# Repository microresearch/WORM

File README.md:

The WORM was for a long time desirous to speake, but the rule and
or∣der of the Court enjoyned him silence, but now strutting and
swelling, and impatient, of further delay, he broke out thus... [Maier]

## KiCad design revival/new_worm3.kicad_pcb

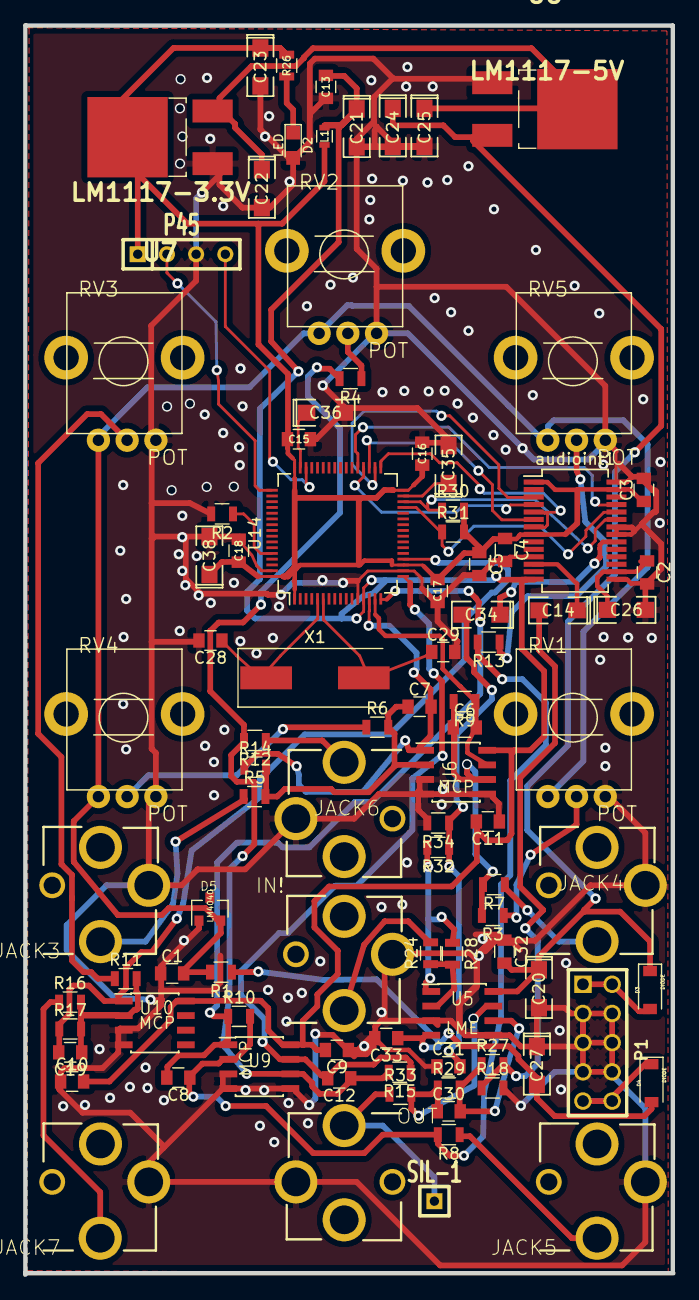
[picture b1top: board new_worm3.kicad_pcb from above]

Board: 2 copper layers, 56.4 x 108.7 mm, 94 parts (0 on the bottom side), 55 nets.

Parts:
C1, C2, C3, C4, C5, C9, C10, C11, C32, C33: 100N; C_0805
C6, C7, C8, C12, C19: 1N; C_0805
C13, C15, C16, C17, C18: 100nF; C_0805
C14, C20, C27, C34: 10u; SMD-1206_Pol1.4mmnew
C21, C22, C23, C24, C25, C26: 10uF; SMD-1206_Pol1.4mmnew
C28, C29: 18pF; C_0805
C30: 22P; C_0805
C31: 220P; C_0805
C35, C36: 2.2uF; SMD-1206_Pol1.4mmnew
C38: 4.7uF; SMD-1206_Pol1.4mmnew
D2: LED; LED_0805
D3, D4: DIODE; D_SOD-123
D5: LM4040; SOT-23
IN!: AUDIO-JACKERTHENVAR_ERTHENVAR-JACK; ERTHENVAR-JACK
JACK3, JACK4, JACK5, JACK6, JACK7: AUDIO-JACKERTHENVAR_ERTHENVAR-JACK; ERTHENVAR-JACK
L1: INDUCTOR; L_0603
OUT: AUDIO-JACKERTHENVAR_ERTHENVAR-JACK; ERTHENVAR-JACK
P1: CONN_5X2; PIN_ARRAY_5x2
P45: SWD; SIL-4
R1: 200R; R_0805
R2: 10K; R_0805
R3, R4, R6, R11, R13: 200K; R_0805
R5, R7, R8, R12, R16: 100K; R_0805
R9, R10, R14, R15, R17: 66.5K; R_0805
R18, R29: 39K; R_0805
R24: 27K; R_0805
R26: 330R; R_0805
R27, R32, R34: 5.6K; R_0805
R28: 33K; R_0805
R30, R31: 4.7K; R_0805
R33: 1K; R_0805
RV1, RV2, RV3, RV4, RV5: POT; RV1
SIL-1: Val**; SIL-1
U5: LME; SOIC-8_3.9x4.9mm_Pitch1.27mm
U6, U9, U10: MCP; SOIC-8_3.9x4.9mm_Pitch1.27mm
U7: LM1117-3.3V; TO-252-2_Rectifier
U8: LM1117-5V; TO-252-2_Rectifier
U14: STM32F405RGT6; LQFP-64_10x10mm_Pitch0.5mm
X1: 8_MHz; Crystal_SMD_HC49-SD
audioint1: AUDIOINT_WM8731; SSOP-28_5.3x10.2mm_Pitch0.65mm

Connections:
+3.3V: C3.1, C4.1, C5.1, C15.1, C16.1, C17.1, C18.1, C23.1, C38.1, L1.2, P45.1, R26.2, R30.2, R31.2, U7.2, U14.1, U14.19, U14.32, U14.48, U14.64, audioint1.1, audioint1.8, audioint1.27
+5V: C22.1, C25.1, U7.3, U8.2
+12V: C20.1, C24.1, C32.2, D3.1, U5.8, U8.3
-12V: C27.2, C33.1, D4.2, R1.1, U5.4
/I2S_LRCK: U14.33, audioint1.5, audioint1.7
/I2S_MCLK: U14.37, audioint1.25
/I2S_SCL: R31.1, U14.29, audioint1.24
/I2S_SCLK: U14.34, audioint1.3
/I2S_SDA: R30.1, U14.30, audioint1.23
/I2S_SDI: U14.35, audioint1.6
/I2S_SDO: U14.36, audioint1.4
/SWCK: P45.2, U14.49
/SWDIO: P45.4, U14.46
/Sheet550B4EA0/CV1: JACK3.3, R5.1
/Sheet550B4EA0/CV2: JACK4.3, R7.1
/Sheet550B4EA0/CV3: JACK5.3, R8.1
/Sheet550B4EA0/CV4: JACK6.3, R12.1
/Sheet550B4EA0/CV5: JACK7.3, R16.1
/Sheet550B4EA0/REF-10: C1.2, D5.2, R1.2, RV1.1, RV2.1, RV3.1, RV4.1, RV5.1
ADC0: C7.2, R14.1, U6.1, U14.14
ADC1: C6.2, R9.1, U6.7, U14.15
ADC2: C8.2, R10.1, U9.1, U14.16
ADC3: C12.2, R15.1, U9.7, U14.17
ADC4: C19.2, R17.1, U10.1, U14.20
AVDD: C9.2, C10.2, C11.2, C13.1, C21.1, L1.1, U6.8, U9.8, U10.8, U14.13, audioint1.14
GND: C1.1, C2.2, C3.2, C4.2, C5.2, C9.1, C10.1, C11.1, C13.2, C15.2, C16.2, C17.2, C18.2, C20.2, C21.2, C22.2, C23.2, C24.2, C25.2, C26.2, C27.1, C28.2, C29.2, C31.1, C32.1, C33.2, C35.2, C36.2, C38.2, D2.2, D5.1, IN!.1@1, JACK3.1@1, JACK4.1@1, JACK5.1@1, JACK6.1@1, JACK7.1@1, OUT.1@1, P1.3, P1.4, P1.5, P1.6, P1.7, P1.8, P45.3, R2.2, R18.2, R34.2, RV1.3, RV2.3, RV3.3, RV4.3, RV5.3, U5.3, U5.5, U6.3, U6.4, U6.5, U7.1, U8.1, U9.3, U9.4, U9.5, U10.3, U10.4, U14.12, U14.18, U14.63, audioint1.11, audioint1.15, audioint1.21, audioint1.22, audioint1.28
LINEINL: C34.1, audioint1.20
LINEOUTL: C14.1, audioint1.12
unnamed: C2.1, C26.1, audioint1.16
unnamed: D2.1, R26.1
unnamed: R2.1, U14.60
unnamed: C28.1, U14.5, X1.1
unnamed: C36.1, U14.47
unnamed: C35.1, U14.31
unnamed: C29.1, U14.6, X1.2
unnamed: D4.1, P1.9, P1.10
unnamed: D3.2, P1.1, P1.2
unnamed: C8.1, R8.2, R10.2, R13.2, U9.2
unnamed: C19.1, R11.2, R16.2, R17.2, U10.2
unnamed: R3.1, RV1.2
unnamed: R4.1, RV2.2
unnamed: IN!.3, R24.2
unnamed: R13.1, RV5.2
unnamed: C12.1, R4.2, R12.2, R15.2, U9.6
unnamed: R11.1, RV3.2
unnamed: C31.2, C34.2, R32.1, R34.1
unnamed: R6.1, RV4.2
unnamed: C7.1, R5.2, R6.2, R14.2, U6.2
unnamed: R24.1, R28.2, U5.2
unnamed: OUT.3, R33.1, SIL-1.1
unnamed: C6.1, R3.2, R7.2, R9.2, U6.6
unnamed: C30.2, R27.1, R29.2, U5.6
unnamed: C14.2, R18.1, R27.2
unnamed: C30.1, R29.1, R33.2, U5.7
unnamed: R28.1, R32.2, U5.1

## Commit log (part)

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2016-01-04 modes
2016-01-06 womr
2016-01-06 dates!
2016-01-13 nvp.c
2016-01-20 nvp_pc add
2016-02-18 notes
2016-02-23 LF modellling
2016-03-10 raven
2016-03-13 xxxxxxxxxxxxxxxx
2016-05-24 added all words LPC/lpc.c
2016-05-25 re---->
2016-05-28 size of panel and pcb redcued
2016-05-29 reducing
2016-05-29 reduce
2016-05-29 aligned
2016-06-01 ti99 works
2016-06-03 apple II echooo
2016-06-08 xxx - new pcb close to finished
2016-06-09 new 003 brd
2016-06-13 generators started
2016-06-14 holmes new not working yet
2016-06-14 now works
2016-06-16 sp0256 tests working almost
2016-06-20 sp0256 in
2016-06-21 triggers
2016-06-22 32k crow coeffs not for WORM though!
2016-06-23 lm4040 change resistor
2016-06-23 vocabss
2016-06-28 worms
2016-07-05 5220
2016-07-07 mame/mess inc tms5200
2016-07-09 huge FIX
2016-07-13 Add files via upload
    c files to output list of characters as list of ints (phoneme representation of the text inputted)
    python files convert phoneme rules from phoneme output to int output => outputs list of phoneme rules in c list format to text file
2016-07-15 digitalk
2016-08-02 Add files via upload
    made outputted rules space delimited, added convert_ascii_table to convert phoneme ascii to integer code ascii, added phoneme_map to decompose
2016-08-02 Add files via upload
    Finished - input array of words from arguments translated to output array of phoneme integer codes
2016-08-29 modes.org
2016-10-18 adc fixings
2016-12-18 xxx_l
2016-12-18 added tubeset
2016-12-18 add from x220
2016-12-18 digitalker roms
2016-12-21 cleanin
2017-01-02 roms
2017-01-04 votrax
2017-01-04 vocabs
2017-01-06 issues
2017-01-10 tron
2017-01-16 back to crow
2017-01-31 sp0256 tests
2017-02-13 x220
2017-02-22 x220 added back in raven stuff
2017-03-03 x220 and some confusion with audio.c
2017-03-06 x220 1v/oct
2017-03-13 t60 as was last!
2017-03-13 x220 NOW!
2017-03-31 t60 ADD MAKEFILE
2017-04-14 t600
2017-04-20 x220 and deleted by mistake
2017-06-19 x220 finalising
2017-06-29 cleaning/testing
2017-06-29 deleting!
2017-07-05 x220 - final tests
2017-07-06 finals
2017-07-10 cleaning
2017-07-11 testing code
2017-07-11 license?
2017-07-25 testings
2017-08-03 closer
2017-08-07 TTS tweaks minor
2017-10-11 minor pre-release fixes
2017-10-18 fixes
2017-10-18 fixes resets
2017-10-19 votrax volume only
2017-11-09 fixed compost freezing
2017-12-04 wormed!
2017-12-05 wormed
2019-09-13 added flash section now to .ld as seemed to need it
2021-06-15 bom and co.
2021-09-30 main.bin corrected
2022-02-26 WORM revival
2022-03-30 new worm pcb
